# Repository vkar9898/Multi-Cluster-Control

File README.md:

# Multi-Cluster-Control
One PCB that controls 7 real car instrument clusters independently, from 1980s analogue gauges requiring AC, to modern CAN-bus dashboards, all running independently from a single ESP32.

# Why I made this
I made this project mostly because I had a lot of car dashboards around, and wanted to use them independently! This would include things such as simply showing time, CPU/GPU temp, HDD write speed, and other things that traditionally take up a spot on the screen. However, it will not be limited to this, as I am also planning on connecting them to racing games like Trackmania Nations Forever, BeamNG (not a racing game), and others. Other than that, I suppose this would just be a fun project. It includes PCB making and a lot of wiring (each cluster has around 20 wires), so I thought it'd be cool, and so far it has been.

# Pictures

# BOM

| Section | Item | Designators / use | Part # / search term | Supplier | Qty | Unit price (USD) | Line total (USD) | Price status | Link | Notes |
|---|---|---|---|---|---|---|---|---|---|---|
| PCB + assembly | Multi-Cluster-Control PCB, 5 boards, 2 assembled (Economic PCBA, 1 oz, top side) | Whole board, all JLC-placed parts | Gerbers + BOM + CPL from Fabrication Toolkit | JLCPCB | 1 | $65.70 | $65.70 | Quoted | [link](https://jlcpcb.com) | PCB $9.80 + PCBA $55.90 |
| PCB + assembly | JLCPCB coupon |  |  | JLCPCB | 1 | -$10.00 | -$10.00 | Quoted |  |  |
| PCB + assembly | Keystone 3568 mini-blade fuse holder (idle parts) | F1, F2 (2 boards) | C5249699 | JLCPCB parts cart | 4 | $1.21 | $4.84 | Quoted | [link](https://jlcpcb.com/partdetail/C5249699) | Idle parts |
| Board parts not assembled by JLC | Cluster plug, 10-pin 3.81 mm screw (KANGNEX WJ15EDGK-3.81-10P-14-00A) | CN1-CN3, 2 per header | C26865 | LCSC | 6 | $0.8112 | $4.87 | Quoted | [link](https://www.lcsc.com/product-detail/C26865.html) |  |
| Board parts not assembled by JLC | Cluster plug, 4-pin 3.81 mm screw (KANGNEX WJ15EDGK-3.81-04P-14-00A) | CN4, 2 per header | C7244 (min order 5) | LCSC | 5 | $0.3071 | $1.54 | Quoted | [link](https://www.lcsc.com/product-detail/C7244.html) | Min order 5 |
| Board parts not assembled by JLC | 5-way screw terminal, 5.08 mm (Phoenix MKDS 1,5/5-5,08, 1715750) | J15 | C6042418 | LCSC | 2 | $1.2721 | $2.54 | Quoted | [link](https://www.lcsc.com/product-detail/C6042418.html) | 1 spare |
| Board parts not assembled by JLC | 1x14 female header 2.54 mm | J11 (VID6606 adapter), 2 per board | C2905420 (min order 5) | LCSC | 5 | $0.1470 | $0.74 | Quoted | [link](https://www.lcsc.com/product-detail/C2905420.html) | Min order 5 |
| Modules and chips | VID6606 stepper driver, SOP-28 (5 pcs) | X-90 speedo stepper driver | VID6606 | AliExpress | 1 | $4.45 | $4.45 | Quoted | [link](https://www.aliexpress.com/item/1005007323081013.html) |  |
| Modules and chips | SOP-28 to DIP-28 adapter boards (10 pcs) | Carrier for the VID6606 in J11 | SOP28 to DIP28 | AliExpress | 1 | $1.64 | $1.64 | Quoted | [link](https://www.aliexpress.com/item/32909339596.html) | 15.24 mm DIP width |
| Modules and chips | X27.168 gauge stepper motor | X-90 speedo + 1 spare | X27.168 | AliExpress | 2 | $2.23 | $4.46 | Quoted | [link](https://www.aliexpress.com/item/1005006620561935.html) |  |
| Modules and chips | PCA9685 16-ch PWM module | J5/J6 (gauge PWM) | PCA9685 | AliExpress | 1 | $3.75 | $3.75 | Quoted | [link](https://www.aliexpress.com/item/1005005670283526.html) |  |
| Modules and chips | MCP2515 CAN module, TJA1050, 8 MHz | Second CAN module | MCP2515 TJA1050 | AliExpress | 1 | $0.88 | $0.88 | Quoted | [link](https://www.aliexpress.com/item/1005010199935143.html) | 8 MHz crystal |
| Modules and chips | MP1584EN adjustable buck module (5 pcs) | M5 (5.0 V), M6 (3.6 V) | MP1584EN | AliExpress | 1 | $3.03 | $3.03 | Quoted | [link](https://www.aliexpress.com/item/1005007653423578.html) | Set voltage before soldering |
| Modules and chips | MT3608 boost module | M7 (24 V) | MT3608 / 1PCS | AliExpress | 1 | $2.21 | $2.21 | Quoted | [link](https://www.aliexpress.com/item/1005011548818999.html) | Set to 24 V |
| Wiring | 20-core 20 AWG RVV sheathed cable, 2 m | 4 cluster cables x 0.5 m | RVV 20 core 20 AWG, 2 m option | AliExpress | 1 | $17.64 | $17.64 | Quoted | [link](https://www.aliexpress.com/item/1005004200589656.html) |  |
| Board parts not assembled by JLC | 2.54 mm pin headers, 1x40 male + 1x40 female (5 of each) | SOP28 adapter pins (2x14), spare headers | 5Sets male female | AliExpress | 1 | $1.77 | $1.77 | Quoted | [link](https://www.aliexpress.com/item/1005008647955410.html) |  |
| Wiring | Dupont jumpers, female-female, 10 cm, 40 pcs | PCA9685, MCP2515 x2, light sensor | Dupont F-F 10 cm | AliExpress | 1 | $0.93 | $0.93 | Quoted | [link](https://www.aliexpress.com/item/1005009372155336.html) |  |
| Power | 12 V 4 A plug pack, 5.5 x 2.1 mm, AU plug | J1, J2 | 4A/12 V/AU Plug | AliExpress | 2 | $3.99 | $7.98 | Quoted | [link](https://www.aliexpress.com/item/1005013455261196.html) | Centre-positive |
| Power | SCA mini blade fuse 5 A, 6 pack | F1, F2 + spares | 726696 | Supercheap Auto | 1 | $2.81 | $2.81 | Quoted | [link](https://www.supercheapauto.com.au/p/sca-sca-automotive-fuses-mini-blade-5-amp-6-pack/726696.html) | Click & collect |
| Lighting | T10 (W5W) LED wedge bulbs, 6500K white, 10 pack | Cluster illumination | ASIN B0HGLD6KBJ | Amazon AU | 1 | $6.33 | $6.33 | Quoted | [link](https://www.amazon.com.au/dp/B0HGLD6KBJ) | Polarised |
| Mounting | M3 x 20 mm pan head screws + nuts + washers, 304 stainless (20 sets) | Board to support, 4 holes | M3 20sets / 20mm | AliExpress | 1 | $3.06 | $3.06 | Quoted | [link](https://www.aliexpress.com/item/4001323750672.html) |  |
| Discounts | AliExpress checkout discounts |  |  | AliExpress | 1 | -$4.32 | -$4.32 | Quoted |  |  |
| Already owned | ESP32 dev board (38-pin) | J3/J4 |  | Owned | 1 | $0.00 | $0.00 | Owned |  |  |
| Already owned | Light sensor module | J14 |  | Owned | 1 | $0.00 | $0.00 | Owned |  |  |
| Already owned | MCP2515 CAN module (first one) | J7 or J9 |  | Owned | 1 | $0.00 | $0.00 | Owned |  |  |
| Shipping | Shipping: UPS Worldwide Express Saver (PCB + assembly + idle parts) |  |  | JLCPCB | 1 | $17.94 | $17.94 | Quoted |  |  |
| Shipping | Shipping: Global Direct Standard Line |  |  | LCSC | 1 | $9.93 | $9.93 | Quoted |  |  |
| Shipping | Shipping: Handling fee |  |  | LCSC | 1 | $3.00 | $3.00 | Quoted |  | Waived over $15.60 merchandise |
| Shipping | Shipping: Dupont jumper store |  |  | AliExpress | 1 | $3.02 | $3.02 | Quoted |  |  |
| Shipping | Shipping: MCP2515 store |  |  | AliExpress | 1 | $2.23 | $2.23 | Quoted |  |  |
| Shipping | Shipping: All other items |  |  | AliExpress | 1 | $0.00 | $0.00 | Quoted |  | Free shipping |
| Shipping | Shipping: Click & collect |  |  | Supercheap Auto | 1 | $0.00 | $0.00 | Quoted |  |  |
| Shipping | Shipping: Standard delivery (T10 bulbs) |  |  | Amazon AU | 1 | $0.00 | $0.00 | Estimate |  | Free on first order or over AU$49 |
 
**Total: $162.97** (parts $126.85 + shipping $36.12)

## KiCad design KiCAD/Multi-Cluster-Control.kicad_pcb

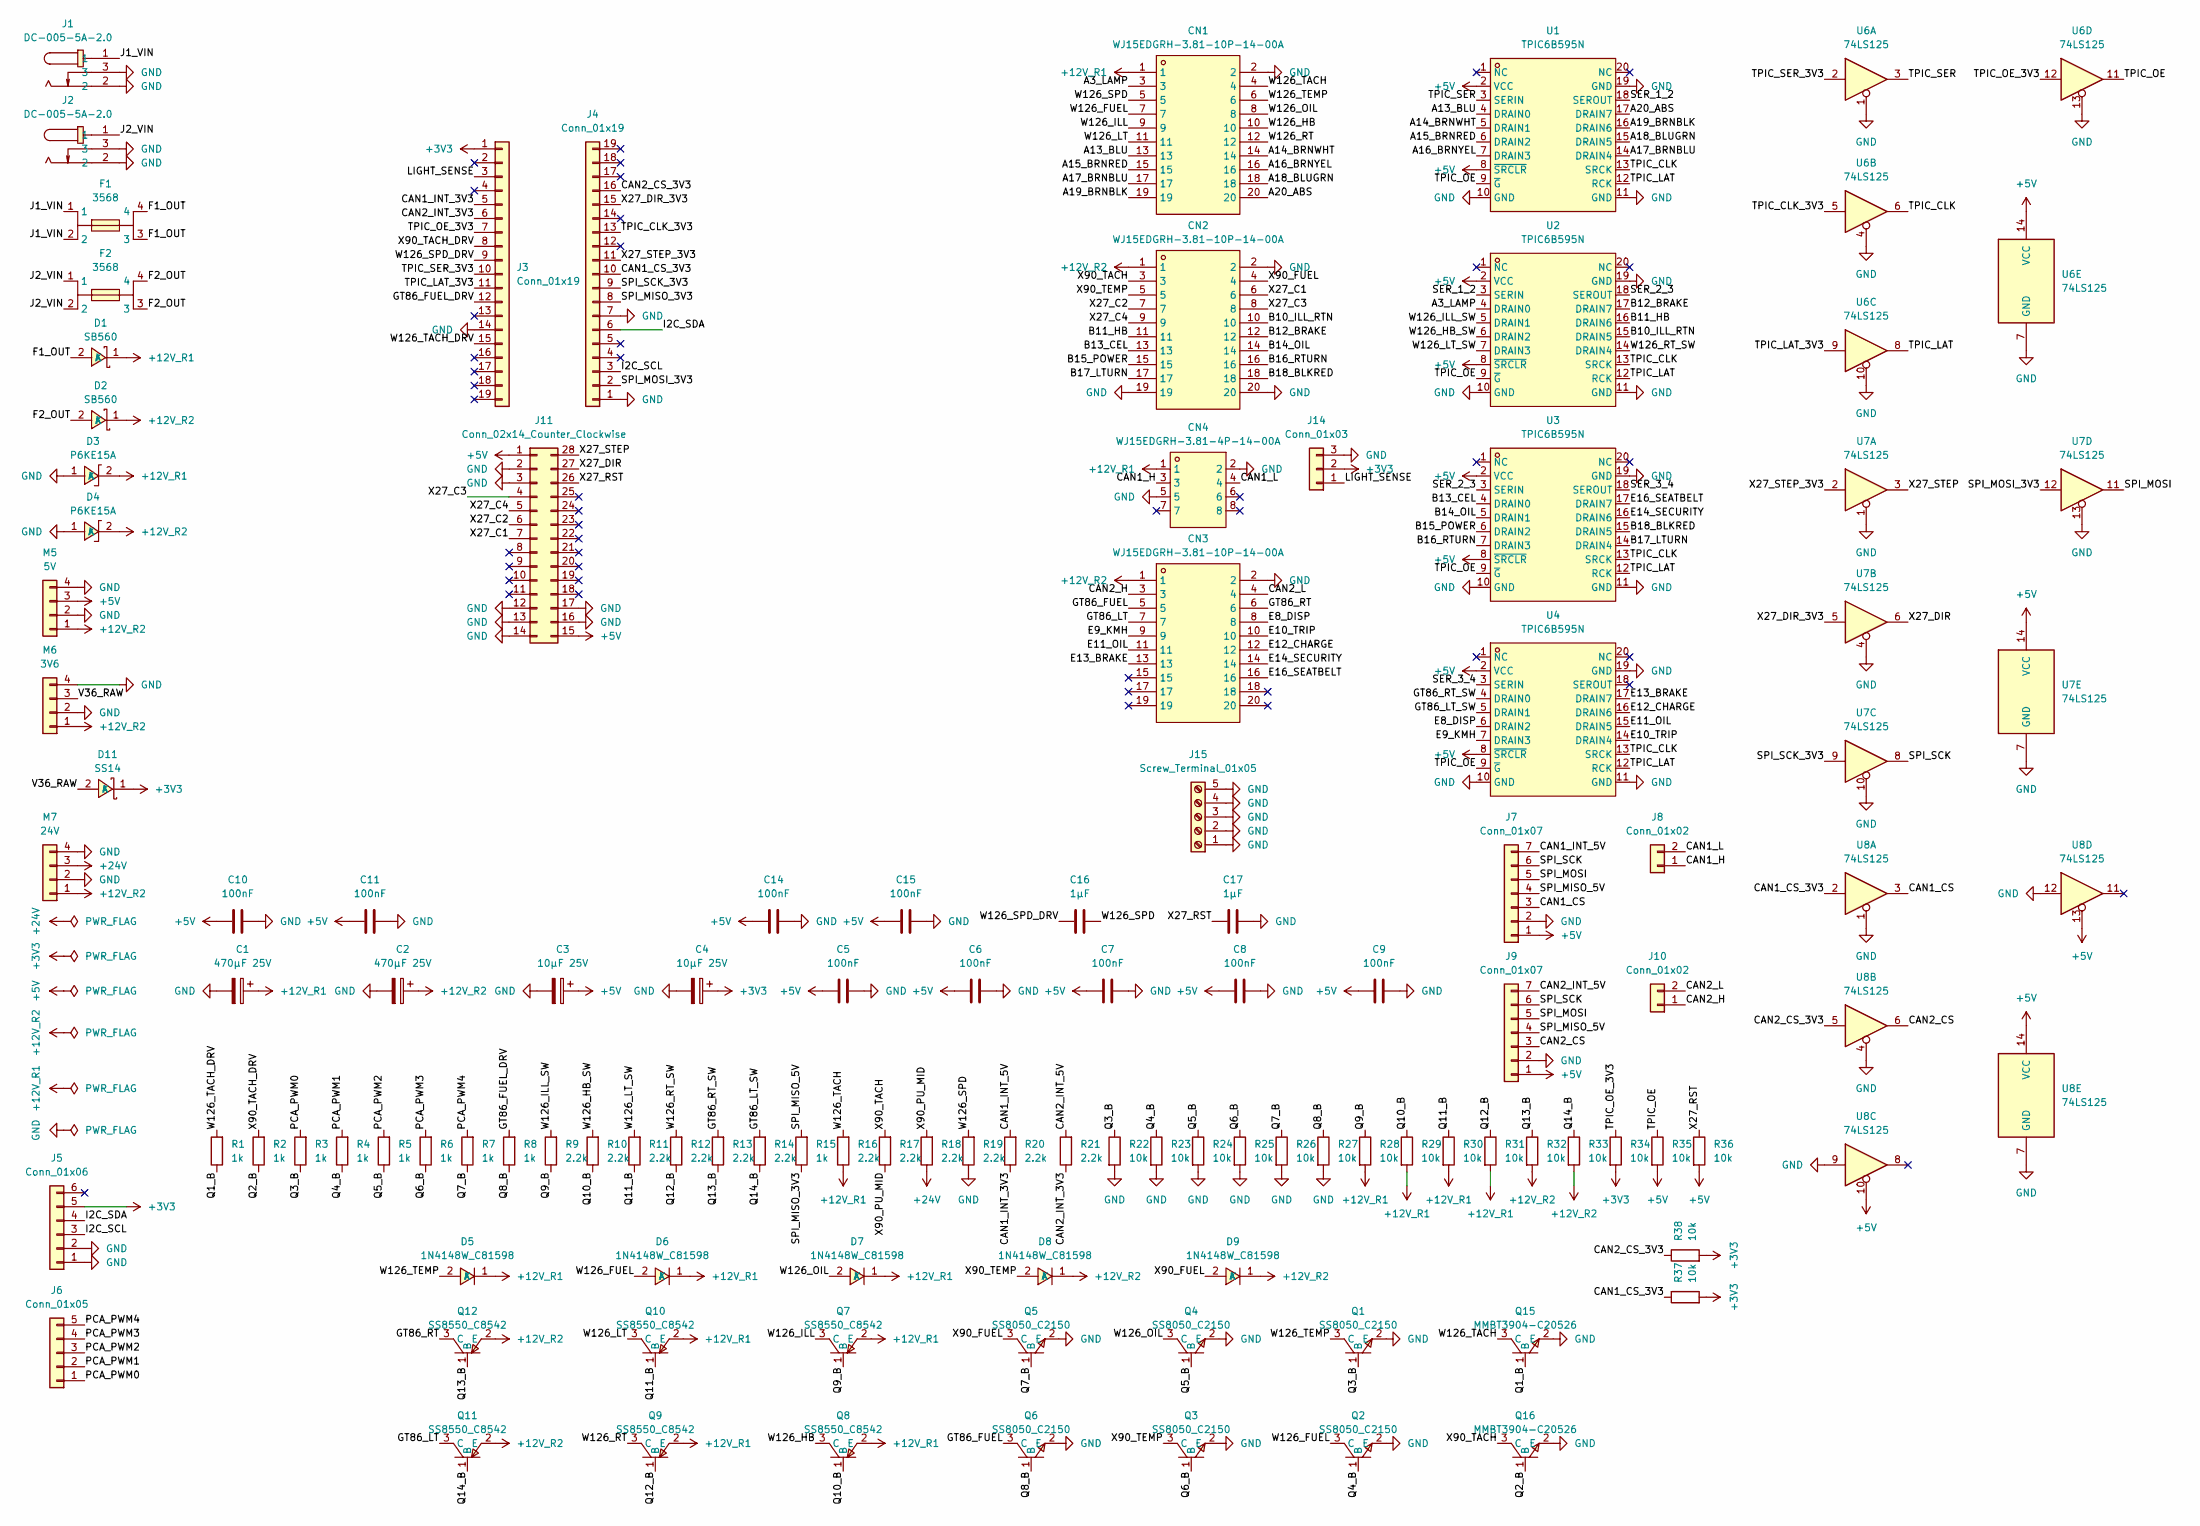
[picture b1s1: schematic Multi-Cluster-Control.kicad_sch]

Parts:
C1, C2: 470µF 25V; CP_Radial_D10.0mm_P5.00mm
C3, C4: 10µF 25V; C_0805_2012Metric; LCSC Part C15850
C5, C6, C7, C8, C9, C10, C11, C14, C15: 100nF; C_0805_2012Metric; LCSC Part C49678
C16, C17: 1µF; C_0805_2012Metric; LCSC Part C28323
CN1, CN2, CN3: WJ15EDGRH-3.81-10P-14-00A; CONN-TH_10P-P3.81_WJ15EDGRH-3.81-10P-14-00A; MPN WJ15EDGRH-3.81-10P-14-00A; LCSC Part C48336
CN4: WJ15EDGRH-3.81-4P-14-00A; CONN-TH_4P-P3.81_WJ15EDGRH-3.81-4P-14-00A; MPN WJ15EDGRH-3.81-04P-14-00A; LCSC Part C26231
D1, D2: SB560; DO-201AD_BD5.3-L8.4-P12.50-D1.4-RD; MPN SB560; LCSC Part C139684
D3, D4: P6KE15A; DO-15_BD3.1-L6.7-P10.70-D0.9-FD; MPN P6KE15A; LCSC Part C10182
D5, D6, D7, D8, D9: 1N4148W_C81598; SOD-123F_L2.7-W1.6-LS3.8-RD; MPN 1N4148W; LCSC Part C81598
D11: SS14; SMA_L4.2-W2.6-LS5.0-RD_1; MPN SS14; LCSC Part C2480
F1, F2: 3568; FUSE-SMD_4P-L16.0-W6.7-P3.40; MPN 3568; LCSC Part C5249699
J1, J2: DC-005-5A-2.0; DC-IN-TH_DC-005-5A-2.0; MPN DC-005-5A-2.0; LCSC Part C381116
J3, J4: Conn_01x19; PinSocket_1x19_P2.54mm_Vertical
J5: Conn_01x06; PinHeader_1x06_P2.54mm_Vertical
J6: Conn_01x05; PinHeader_1x05_P2.54mm_Vertical
J7, J9: Conn_01x07; PinHeader_1x07_P2.54mm_Vertical
J8, J10: Conn_01x02; PinHeader_1x02_P2.54mm_Vertical
J11: Conn_02x14_Counter_Clockwise; DIP-28_W15.24mm_Socket
J14: Conn_01x03; PinHeader_1x03_P2.54mm_Vertical
J15: Screw_Terminal_01x05; TerminalBlock_Phoenix_MKDS-1,5-5-5.08_1x05_P5.08mm_Horizont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
M5: 5V; PinHeader_1x04_P2.54mm_Vertical
M6: 3V6; PinHeader_1x04_P2.54mm_Vertical
M7: 24V; PinHeader_1x04_P2.54mm_Vertical
Q1, Q2, Q3, Q4, Q5, Q6: SS8050_C2150; SOT-23-3_L2.9-W1.3-P1.90-LS2.4-BR; MPN SS8050(RANGE:200-350); LCSC Part C2150
Q7, Q8, Q9, Q10, Q11, Q12: SS8550_C8542; SOT-23-3_L2.9-W1.3-P1.90-LS2.4-BR; MPN SS8550 Y2(RANGE:200-350); LCSC Part C8542
Q15, Q16: MMBT3904-C20526; SOT-23-3_L2.9-W1.3-P1.90-LS2.4-BR; MPN MMBT3904(RANGE:100-300); LCSC Part C20526
R1, R2, R3, R4, R5, R6, R7, R8, R15: 1k; R_0805_2012Metric; LCSC Part C17513
R9, R10, R11, R12, R13, R14, R16, R17, R18, R19, R20, R21: 2.2k; R_0805_2012Metric; LCSC Part C17520
R22, R23, R24, R25, R26, R27, R28, R29, R30, R31, R32, R33, R34, R35, R36, R37, R38: 10k; R_0805_2012Metric; LCSC Part C17414
U1, U2, U3, U4: TPIC6B595N; SOIC-20W_7.5x12.8mm_P1.27mm; MPN TPIC6B595N; LCSC Part C7094
U6, U7, U8: 74LS125; SOIC-14_3.9x8.7mm_P1.27mm; LCSC Part C5962

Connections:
+3V3: C4.1, D11.1 (K), J3.1, J5.5, J14.2, R34.2, R37.2, R38.2
+5V: C3.1, C5.2, C6.2, C7.2, C8.2, C9.2, C10.2, C11.2, C14.2, C15.2, J7.1, J9.1, J11.1, J11.15, M5.3, R35.2, R36.2, U1.2 (VCC), U1.8 (~SRCLR), U2.2 (VCC), U2.8 (~SRCLR), U3.2 (VCC), U3.8 (~SRCLR), U4.2 (VCC), U4.8 (~SRCLR), U6.14 (VCC), U7.14 (VCC), U8.10, U8.13, U8.14 (VCC)
+12V_R1: C1.1, CN1.1, CN4.1, D1.1 (K), D3.2 (K), D5.1 (K), D6.1 (K), D7.1 (K), Q7.2 (E), Q8.2 (E), Q9.2 (E), Q10.2 (E), R16.1, R28.2, R29.2, R30.2, R31.2
+12V_R2: C2.1, CN2.1, CN3.1, D2.1 (K), D4.2 (K), D8.1 (K), D9.1 (K), M5.1, M6.1, M7.1, Q11.2 (E), Q12.2 (E), R32.2, R33.2
+24V: M7.3, R18.1
/A3_LAMP: CN1.3, U2.4 (DRAIN0)
/A13_BLU: CN1.13, U1.4 (DRAIN0)
/A14_BRNWHT: CN1.14, U1.5 (DRAIN1)
/A15_BRNRED: CN1.15, U1.6 (DRAIN2)
/A16_BRNYEL: CN1.16, U1.7 (DRAIN3)
/A17_BRNBLU: CN1.17, U1.14 (DRAIN4)
/A18_BLUGRN: CN1.18, U1.15 (DRAIN5)
/A19_BRNBLK: CN1.19, U1.16 (DRAIN6)
/A20_ABS: CN1.20, U1.17 (DRAIN7)
/B10_ILL_RTN: CN2.10, U2.15 (DRAIN5)
/B11_HB: CN2.11, U2.16 (DRAIN6)
/B12_BRAKE: CN2.12, U2.17 (DRAIN7)
/B13_CEL: CN2.13, U3.4 (DRAIN0)
/B14_OIL: CN2.14, U3.5 (DRAIN1)
/B15_POWER: CN2.15, U3.6 (DRAIN2)
/B16_RTURN: CN2.16, U3.7 (DRAIN3)
/B17_LTURN: CN2.17, U3.14 (DRAIN4)
/B18_BLKRED: CN2.18, U3.15 (DRAIN5)
/CAN1_CS: J7.3, U8.3
/CAN1_CS_3V3: J4.10, R37.1, U8.2
/CAN1_H: CN4.3, J8.1
/CAN1_INT_3V3: J3.5, R20.1
/CAN1_INT_5V: J7.7, R20.2
/CAN1_L: CN4.4, J8.2
/CAN2_CS: J9.3, U8.6
/CAN2_CS_3V3: J4.16, R38.1, U8.5
/CAN2_H: CN3.3, J10.1
/CAN2_INT_3V3: J3.6, R21.1
/CAN2_INT_5V: J9.7, R21.2
/CAN2_L: CN3.4, J10.2
/E8_DISP: CN3.8, U4.6 (DRAIN2)
/E9_KMH: CN3.9, U4.7 (DRAIN3)
/E10_TRIP: CN3.10, U4.14 (DRAIN4)
/E11_OIL: CN3.11, U4.15 (DRAIN5)
/E12_CHARGE: CN3.12, U4.16 (DRAIN6)
/E13_BRAKE: CN3.13, U4.17 (DRAIN7)
/E14_SECURITY: CN3.14, U3.16 (DRAIN6)
/E16_SEATBELT: CN3.16, U3.17 (DRAIN7)
/F1_OUT: D1.2 (A), F1.3, F1.4
/F2_OUT: D2.2 (A), F2.3, F2.4
/GT86_FUEL: CN3.5, Q6.3 (C)
/GT86_FUEL_DRV: J3.12, R8.2
/GT86_LT: CN3.7, Q11.3 (C)
/GT86_LT_SW: R14.2, U4.5 (DRAIN1)
/GT86_RT: CN3.6, Q12.3 (C)
/GT86_RT_SW: R13.2, U4.4 (DRAIN0)
/I2C_SCL: J4.3, J5.3
/I2C_SDA: J4.6, J5.4
/J1_VIN: F1.1, F1.2, J1.1
/J2_VIN: F2.1, F2.2, J2.1
/LIGHT_SENSE: J3.3, J14.1
/PCA_PWM0: J6.1, R3.2
/PCA_PWM1: J6.2, R4.2
/PCA_PWM2: J6.3, R5.2
/PCA_PWM3: J6.4, R6.2
/PCA_PWM4: J6.5, R7.2
/Q1_B: Q15.1 (B), R1.1
/Q2_B: Q16.1 (B), R2.1
/Q3_B: Q1.1 (B), R3.1, R22.1
/Q4_B: Q2.1 (B), R4.1, R23.1
/Q5_B: Q4.1 (B), R5.1, R24.1
/Q6_B: Q3.1 (B), R6.1, R25.1
/Q7_B: Q5.1 (B), R7.1, R26.1
/Q8_B: Q6.1 (B), R8.1, R27.1
/Q9_B: Q7.1 (B), R9.1, R28.1
/Q10_B: Q8.1 (B), R10.1, R29.1
/Q11_B: Q10.1 (B), R11.1, R30.1
/Q12_B: Q9.1 (B), R12.1, R31.1
/Q13_B: Q12.1 (B), R13.1, R32.1
/Q14_B: Q11.1 (B), R14.1, R33.1
/SER_1_2: U1.18 (SEROUT), U2.3 (SERIN)
/SER_2_3: U2.18 (SEROUT), U3.3 (SERIN)
/SER_3_4: U3.18 (SEROUT), U4.3 (SERIN)
/SPI_MISO_3V3: J4.8, R15.1
/SPI_MISO_5V: J7.4, J9.4, R15.2
/SPI_MOSI: J7.5, J9.5, U7.11
/SPI_MOSI_3V3: J4.2, U7.12
/SPI_SCK: J7.6, J9.6, U7.8
/SPI_SCK_3V3: J4.9, U7.9
/TPIC_CLK: U1.13 (SRCK), U2.13 (SRCK), U3.13 (SRCK), U4.13 (SRCK), U6.6
/TPIC_CLK_3V3: J4.13, U6.5
/TPIC_LAT: U1.12 (RCK), U2.12 (RCK), U3.12 (RCK), U4.12 (RCK), U6.8
/TPIC_LAT_3V3: J3.11, U6.9
/TPIC_OE: R35.1, U1.9 (~G), U2.9 (~G), U3.9 (~G), U4.9 (~G), U6.11
/TPIC_OE_3V3: J3.7, R34.1, U6.12
/TPIC_SER: U1.3 (SERIN), U6.3
/TPIC_SER_3V3: J3.10, U6.2
/V36_RAW: D11.2 (A), M6.3
/W126_FUEL: CN1.7, D6.2 (A), Q2.3 (C)
/W126_HB: CN1.10, Q8.3 (C)
/W126_HB_SW: R10.2, U2.6 (DRAIN2)
/W126_ILL: CN1.9, Q7.3 (C)
/W126_ILL_SW: R9.2, U2.5 (DRAIN1)
/W126_LT: CN1.11, Q10.3 (C)
/W126_LT_SW: R11.2, U2.7 (DRAIN3)
/W126_OIL: CN1.8, D7.2 (A), Q4.3 (C)
/W126_RT: CN1.12, Q9.3 (C)
/W126_RT_SW: R12.2, U2.14 (DRAIN4)
/W126_SPD: C16.1, CN1.5, R19.2
/W126_SPD_DRV: C16.2, J3.9
/W126_TACH: CN1.4, Q15.3 (C), R16.2
/W126_TACH_DRV: J3.15, R1.2
/W126_TEMP: CN1.6, D5.2 (A), Q1.3 (C)
/X27_C1: CN2.6, J11.7
/X27_C2: CN2.7, J11.6
/X27_C3: CN2.8, J11.4
/X27_C4: CN2.9, J11.5
/X27_DIR: J11.27, U7.6
/X27_DIR_3V3: J4.15, U7.5
/X27_RST: C17.2, J11.26, R36.1
/X27_STEP: J11.28, U7.3
/X27_STEP_3V3: J4.11, U7.2
/X90_FUEL: CN2.4, D9.2 (A), Q5.3 (C)
/X90_PU_MID: R17.1, R18.2
/X90_TACH: CN2.3, Q16.3 (C), R17.2
/X90_TACH_DRV: J3.8, R2.2
/X90_TEMP: CN2.5, D8.2 (A), Q3.3 (C)
GND: C1.2, C2.2, C3.2, C4.2, C5.1, C6.1, C7.1, C8.1, C9.1, C10.1, C11.1, C14.1, C15.1, C17.1, CN1.2, CN2.2, CN2.19, CN2.20, CN3.2, CN4.2, CN4.5, D3.1 (A), D4.1 (A), J1.2, J1.3, J2.2, J2.3, J3.14, J4.1, J4.7, J5.1, J5.2, J7.2, J9.2, J11.2, J11.3, J11.12, J11.13, J11.14, J11.16, J11.17, J14.3, J15.1, J15.2, J15.3, J15.4, J15.5, M5.2, M5.4, M6.2, M6.4, M7.2, M7.4, Q1.2 (E), Q2.2 (E), Q3.2 (E), Q4.2 (E), Q5.2 (E), Q6.2 (E), Q15.2 (E), Q16.2 (E), R19.1, R22.2, R23.2, R24.2, R25.2, R26.2, R27.2, U1.10 (GND), U1.11 (GND), U1.19 (GND), U2.10 (GND), U2.11 (GND), U2.19 (GND), U3.10 (GND), U3.11 (GND), U3.19 (GND), U4.10 (GND), U4.11 (GND), U4.19 (GND), U6.1, U6.4, U6.7 (GND), U6.10, U6.13, U7.1, U7.4, U7.7 (GND), U7.10, U7.13, U8.1, U8.4, U8.7 (GND), U8.9, U8.12

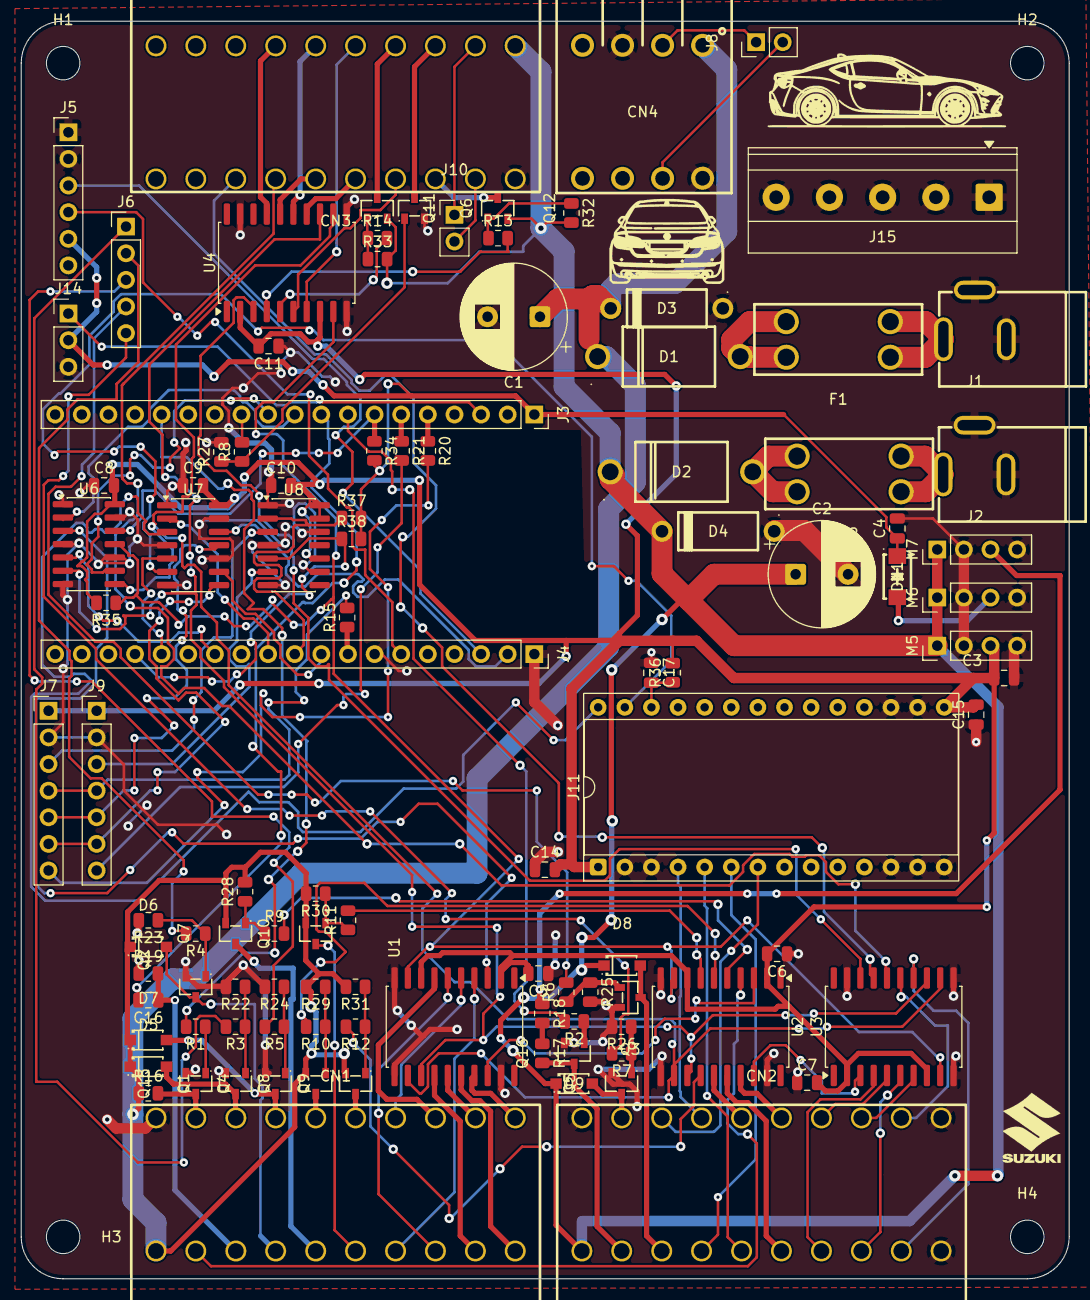
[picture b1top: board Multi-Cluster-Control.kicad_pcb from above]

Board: 2 copper layers, 100.0 x 120.0 mm, 110 parts (0 on the bottom side), 123 nets.

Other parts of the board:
H1, H2, H3, H4: MountingHole_3.2mm_M3

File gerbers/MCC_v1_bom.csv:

Designator,Footprint,Quantity,Value,LCSC Part #
"C1, C2",CP_Radial_D10.0mm_P5.00mm,2,470µF 25V,
"C10, C11, C14, C15, C5, C6, C7, C8, C9",0805,9,100nF,C49678
"C16, C17",0805,2,1µF,C28323
"C3, C4",0805,2,10µF 25V,C15850
"CN1, CN2, CN3",CONN-TH_10P-P3.81_WJ15EDGRH-3.81-10P-14-00A,3,WJ15EDGRH-3.81-10P-14-00A,C48336
CN4,CONN-TH_4P-P3.81_WJ15EDGRH-3.81-4P-14-00A,1,WJ15EDGRH-3.81-4P-14-00A,C26231
"D1, D2",DO-201AD_BD5.3-L8.4-P12.50-D1.4-RD,2,SB560,C139684
D11,SMA_L4.2-W2.6-LS5.0-RD_1,1,SS14,C2480
"D3, D4",DO-15_BD3.1-L6.7-P10.70-D0.9-FD,2,P6KE15A,C10182
"D5, D6, D7, D8, D9",SOD-123F_L2.7-W1.6-LS3.8-RD,5,1N4148W_C81598,C81598
"F1, F2",FUSE-SMD_4P-L16.0-W6.7-P3.40,2,3568,C5249699
"J1, J2",DC-IN-TH_DC-005-5A-2.0,2,DC-005-5A-2.0,C381116
"J10, J8",PinHeader_1x02_P2.54mm_Vertical,2,Conn_01x02,
J11,DIP-28_W15.24mm_Socket,1,Conn_02x14_Counter_Clockwise,
J14,PinHeader_1x03_P2.54mm_Vertical,1,Conn_01x03,
J15,"TerminalBlock_Phoenix_MKDS-1,5-5-5.08_1x05_P5.08mm_Horizontal",1,Screw_Terminal_01x05,
"J3, J4",PinSocket_1x19_P2.54mm_Vertical,2,Conn_01x19,
J5,PinHeader_1x06_P2.54mm_Vertical,1,Conn_01x06,
J6,PinHeader_1x05_P2.54mm_Vertical,1,Conn_01x05,
"J7, J9",PinHeader_1x07_P2.54mm_Vertical,2,Conn_01x07,
M5,PinHeader_1x04_P2.54mm_Vertical,1,5V,
M6,PinHeader_1x04_P2.54mm_Vertical,1,3V6,
M7,PinHeader_1x04_P2.54mm_Vertical,1,24V,
"Q1, Q2, Q3, Q4, Q5, Q6",SOT-23-3_L2.9-W1.3-P1.90-LS2.4-BR,6,SS8050_C2150,C2150
"Q10, Q11, Q12, Q7, Q8, Q9",SOT-23-3_L2.9-W1.3-P1.90-LS2.4-BR,6,SS8550_C8542,C8542
"Q15, Q16",SOT-23-3_L2.9-W1.3-P1.90-LS2.4-BR,2,MMBT3904-C20526,C20526
"R1, R15, R2, R3, R4, R5, R6, R7, R8",0805,9,1k,C17513
"R10, R11, R12, R13, R14, R16, R17, R18, R19, R20, R21, R9",0805,12,2.2k,C17520
"R22, R23, R24, R25, R26, R27, R28, R29, R30, R31, R32, R33, R34, R35, R36, R37, R38",0805,17,10k,C17414
"U1, U2, U3, U4",SOIC-20W_7.5x12.8mm_P1.27mm,4,TPIC6B595N,C7094
"U6, U7, U8",SOIC-14_3.9x8.7mm_P1.27mm,3,74LS125,C5962

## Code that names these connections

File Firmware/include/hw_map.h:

#pragma once
#include <stdint.h>

constexpr uint8_t PIN_TPIC_SER  = 26;
constexpr uint8_t PIN_TPIC_CLK  = 4;
constexpr uint8_t PIN_TPIC_LAT  = 27;
constexpr uint8_t PIN_TPIC_OE   = 32;  // active low

constexpr uint8_t PIN_W126_TACH = 13;
constexpr uint8_t PIN_X90_TACH  = 33;
constexpr uint8_t PIN_W126_SPD  = 25;
constexpr uint8_t PIN_GT86_FUEL = 14;

constexpr uint8_t PIN_X27_STEP  = 17;
constexpr uint8_t PIN_X27_DIR   = 2;

constexpr uint8_t PIN_SPI_SCK   = 18;
constexpr uint8_t PIN_SPI_MOSI  = 23;
constexpr uint8_t PIN_SPI_MISO  = 19;
constexpr uint8_t PIN_CAN1_CS   = 5;
constexpr uint8_t PIN_CAN1_INT  = 34;
constexpr uint8_t PIN_CAN2_CS   = 15;
constexpr uint8_t PIN_CAN2_INT  = 35;

constexpr uint8_t PIN_I2C_SDA   = 21;
constexpr uint8_t PIN_I2C_SCL   = 22;
constexpr uint8_t PIN_LIGHT     = 36;

// even channels so each gets its own timer
constexpr uint8_t LEDC_W126_TACH = 0;
constexpr uint8_t LEDC_X90_TACH  = 2;
constexpr uint8_t LEDC_W126_SPD  = 4;
constexpr uint8_t LEDC_GT86_FUEL = 6;
constexpr uint32_t GT86_FUEL_HZ  = 31000;

constexpr uint32_t MCP2515_CRYSTAL_HZ = 8000000;
constexpr uint32_t CAN_BITRATE        = 500000;

constexpr uint8_t  PCA_ADDR       = 0x40;
constexpr uint16_t PCA_DEFAULT_HZ = 1000;
constexpr uint16_t PCA_MAX_HZ     = 1526;
constexpr uint16_t PCA_MIN_HZ     = 24;

enum PcaChannel : uint8_t {
  PCA_W126_TEMP = 0,
  PCA_W126_FUEL = 1,
  PCA_W126_OIL  = 2,  // inverted
  PCA_X90_TEMP  = 3,
  PCA_X90_FUEL  = 4,
  PCA_X90_ODOFF = 5,
};

constexpr uint32_t TURN_HALF_MS = 333;

// bit = chip * 8 + drain
enum TpicBit : uint8_t {
  W126_BATTERY    = 0,
  W126_BRAKEFLUID = 1,
  W126_PADWEAR    = 2,
  W126_COOLANT    = 3,
  W126_WASHER     = 4,
  W126_FUELRES    = 5,
  W126_OILLEVEL   = 6,  // inverted
  W126_ABS        = 7,
  W126_BULBFAIL   = 8,
  W126_ILL        = 9,
  W126_HB         = 10,
  W126_LEFT       = 11,
  W126_RIGHT      = 12,
  X90_ILL         = 13,  // current limit
  X90_HB          = 14,
  X90_BRAKE       = 15,
  X90_CEL         = 16,
  X90_OIL         = 17,
  X90_POWER       = 18,
  X90_RIGHT       = 19,
  X90_LEFT        = 20,
  X90_CHARGE      = 21,
  GT86_SECURITY   = 22,
  GT86_SEATBELT   = 23,
  GT86_RIGHT      = 24,
  GT86_LEFT       = 25,
  X90_SEATBELT    = 26,
  X90_4WD         = 27,
  GT86_TRIP       = 28,
  GT86_OIL        = 29,
  GT86_CHARGE     = 30,
  GT86_BRAKE      = 31,
};

struct TpicName { uint8_t bit; const char *name; };
static const TpicName TPIC_NAMES[32] = {
  {W126_BATTERY,    "W126 battery/charge lamp"},
  {W126_BRAKEFLUID, "W126 brake fluid/park brake lamp"},
  {W126_PADWEAR,    "W126 pad wear lamp"},
  {W126_COOLANT,    "W126 coolant level lamp"},
  {W126_WASHER,     "W126 washer fluid lamp"},
  {W126_FUELRES,    "W126 fuel reserve lamp"},
  {W126_OILLEVEL,   "W126 oil level lamp (inverted)"},
  {W126_ABS,        "W126 ABS lamp"},
  {W126_BULBFAIL,   "W126 bulb-failure lamp"},
  {W126_ILL,        "W126 illumination"},
  {W126_HB,         "W126 high beam"},
  {W126_LEFT,       "W126 left turn"},
  {W126_RIGHT,      "W126 right turn"},
  {X90_ILL,         "X-90 illumination"},
  {X90_HB,          "X-90 high beam"},
  {X90_BRAKE,       "X-90 brake"},
  {X90_CEL,         "X-90 check engine"},
  {X90_OIL,         "X-90 oil pressure"},
  {X90_POWER,       "X-90 power mode"},
  {X90_RIGHT,       "X-90 right turn"},
  {X90_LEFT,        "X-90 left turn"},
  {X90_CHARGE,      "X-90 charge"},
  {GT86_SECURITY,   "GT86 security lamp"},
  {GT86_SEATBELT,   "GT86 seatbelt lamp"},
  {GT86_RIGHT,      "GT86 right turn"},
  {GT86_LEFT,       "GT86 left turn"},
  {X90_SEATBELT,    "X-90 seat belt"},
  {X90_4WD,         "X-90 4WD"},
  {GT86_TRIP,       "GT86 TRIP button"},
  {GT86_OIL,        "GT86 oil lamp"},
  {GT86_CHARGE,     "GT86 charge lamp"},
  {GT86_BRAKE,      "GT86 brake lamp"},
};
